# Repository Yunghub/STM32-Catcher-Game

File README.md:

# Catch the Ball Game

Catch the Ball is an embedded system game that runs on an STM32 microcontroller. This project uses an 11x7 LED matrix, a joystick, and a speaker to deliver an interactive gaming experience where the player controls a paddle to catch falling objects.

## Features

- **LED Matrix Display:** An 11x7 LED matrix shows the game graphics.
- **Joystick Control:** Move the paddle using analog joystick inputs.
- **Sound Effects:** Non-blocking PWM beeps provide audio feedback when catching an object.
- **Dynamic Game Speed:** The game accelerates as the player's score increases.
- **Button Interactions:**
  - **B1:** Toggle pause/resume.
  - **PB5:** Increase game speed on a short press and trigger a game-over sequence on a long press.

## Hardware Requirements

- **Microcontroller Board:** NUCLEO-F401RE.
- **Display:** 11x7 LED Matrix.
- **Input Devices:** Analog joystick, push buttons (B1 and PB5).
- **Audio:** Speaker for sound effects.
- **PCB:** PCB design files are available in the `PCB` folder.
- **Programming Tool:** ST-Link or any compatible programmer/debugger.

## Software Requirements

- STM32 HAL libraries
- STM32CubeMX for initial configuration
- GCC toolchain or a compatible ARM development toolchain

## Project Structure

- **main.c:** Contains the main game loop, initialization code, and interrupt callbacks.
- **ledmatrix.h:** Header file for interfacing with the LED matrix (ensure this file is present in your project).
- **PCB Folder:** Contains the PCB design files.
- **HAL and other peripheral configuration files:** Automatically generated by STM32CubeMX.

## How to Build and Flash

1. **Import the Project:**
   - Open the project in your preferred IDE (e.g., STM32CubeIDE).
2. **Configure the Project:**
   - Verify the microcontroller settings and ensure that all peripherals (ADC, TIM, I2C, UART, GPIO) are correctly configured.
3. **Build the Project:**
   - Compile the project using the IDE’s build system.
4. **Flash the Firmware:**
   - Connect your NUCLEO-F401RE board via ST-Link and flash the compiled firmware.

## How to Play

- **Move the Paddle:** Use the joystick to shift the paddle left or right.
- **Catch Falling Objects:** Position your paddle under the falling object to catch it.
- **Increase Score and Speed:** Each successful catch increases the score and slightly speeds up the game.
- **Game Over:**
  - A long press on the PB5 button triggers a game-over sequence, displaying the final score.
  - Releasing PB5 after a short press will increase the game speed.

## Code Overview

- **Joystick Handling:** ADC with DMA is used to read the X and Y values, controlling the paddle’s position.
- **LED Matrix Updates:** The screen is cleared and redrawn in every loop iteration to reflect the current game state.
- **Audio Feedback:** PWM via TIM3 is used to produce beeps; the pitch varies with the player’s score.
- **Interrupts:** External interrupts on buttons manage pausing and game control actions.

## License

This project is licensed under the [MIT License](LICENSE).

## Author

- **Yung**

## Acknowledgments

- Special thanks to the STM32 community and open-source contributors for the invaluable resources and libraries that made this project possible.

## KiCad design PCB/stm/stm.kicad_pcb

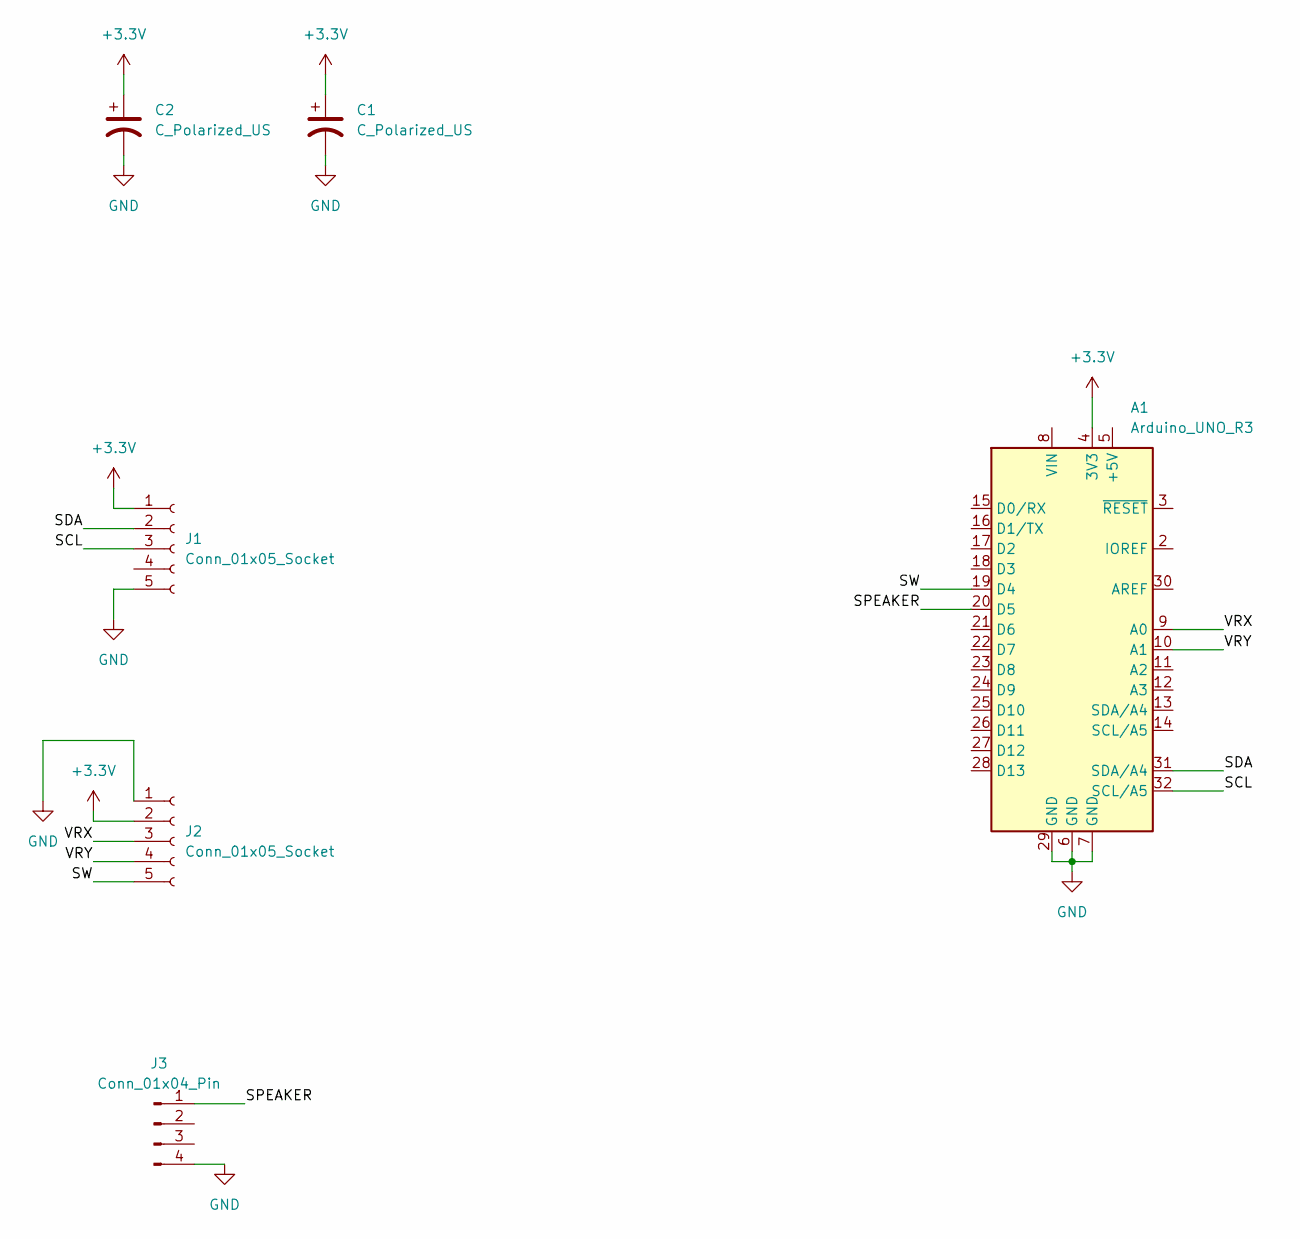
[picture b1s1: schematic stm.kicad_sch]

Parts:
A1: Arduino_UNO_R3
C1, C2: C_Polarized_US; CP_Elec_8x11.9
J1, J2: Conn_01x05_Socket; PinHeader_1x05_P2.54mm_Vertical
J3: Conn_01x04_Pin; PinHeader_1x04_P2.54mm_Vertical

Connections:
+3.3V: A1.4 (3V3), C1.1, C2.1, J1.1, J2.2
/SCL: A1.32 (SCL/A5), J1.3
/SDA: A1.31 (SDA/A4), J1.2
/SPEAKER: A1.20 (D5), J3.1
/SW: A1.19 (D4), J2.5
/VRX: A1.9 (A0), J2.3
/VRY: A1.10 (A1), J2.4
GND: A1.6 (GND), A1.7 (GND), A1.29 (GND), C1.2, C2.2, J1.5, J2.1, J3.4

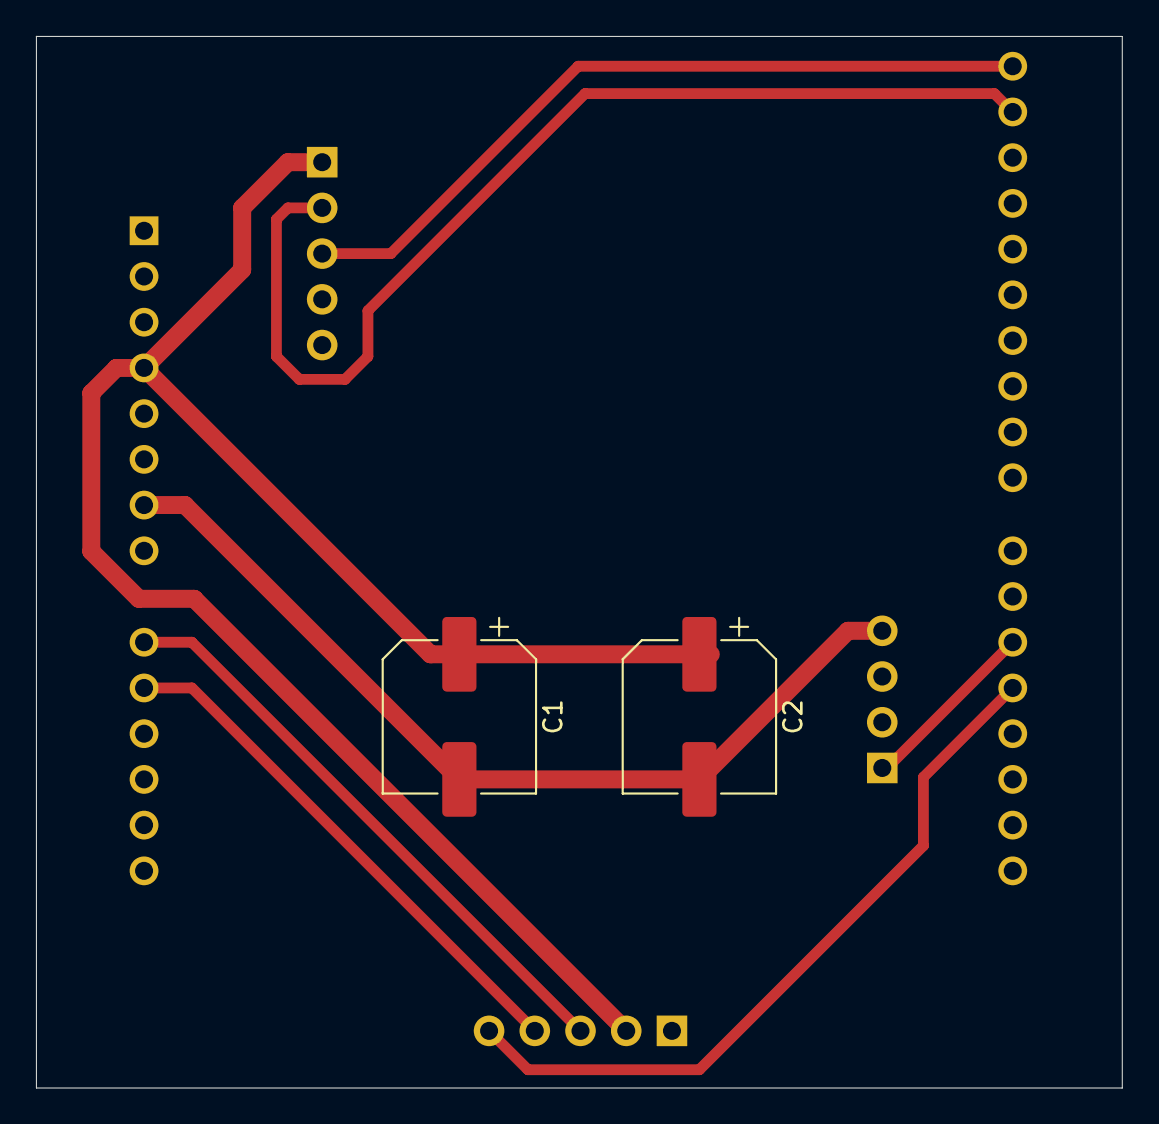
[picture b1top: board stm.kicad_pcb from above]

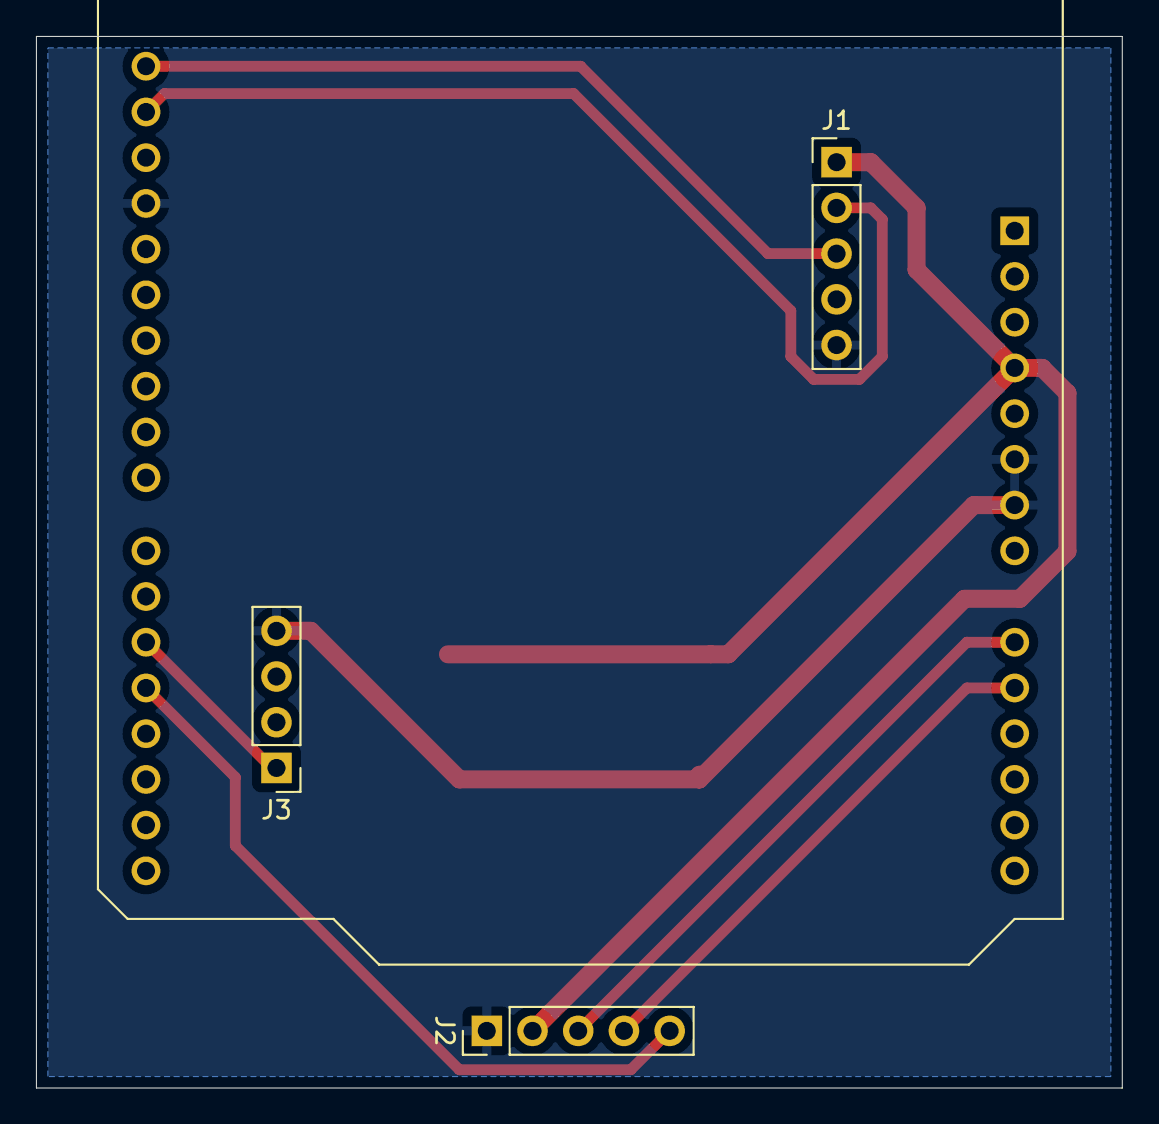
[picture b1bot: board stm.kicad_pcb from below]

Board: 2 copper layers, 60.3 x 58.4 mm, 6 parts (4 on the bottom side), 8 nets.

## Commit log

2025-03-19 Added piezo speaker, pause button, and speed up button
2025-03-26 Added Multifunction
2025-03-26 Seperated Header File
2025-03-29 Added GIF
